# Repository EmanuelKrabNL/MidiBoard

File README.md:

# MIDIBOARD
## What is this project?
Well, basically a simplified mini keyboard for my little sister.
Shes saying she wants to play piano, so i built her one! (Hopefully she wanted to play the piano because her cool brother also plays drums and piano, *rightttt..???*)
-# Im so funny i know right
Okay, back to the plot, i made this becuase she wants a piano (just to press some keys and never touch it again), so we are making here one! (we are so back)

## What does it do?
When you press the 'key looking things', while it is connected to a midi input supporting device, and the midi supporting device is actively running a midi supported application, and the firmware which makes the midi device input for the midi supporting device running the midi supported application is flashed, it should be ready to go! 
-# omg im so funny

## Why is this suited for my little sister?
I have put the letters of the notes on the midi device which is supported by the midi- okay ill stop... ;-; Okay, so, the letters give my little sister an indication of what note she is playing, and i have also decided to make a higher note actually higher! That way she knows how high or low a note will sound like without thinking!

## What can my midiboard do?
The left mechanical switch makes you go an octave lower, the right one makes you go an octave higher, and the middle one plays a random key!
The left slider 'does' the audio/volume, and the right one modulation!
Ive also added lights cause why not!

## Why have i made this?
For my lil sis, *duhhh...*

## What is its purpose?
***insert musical sounds and off key piano notes being played by a grizzly bear***

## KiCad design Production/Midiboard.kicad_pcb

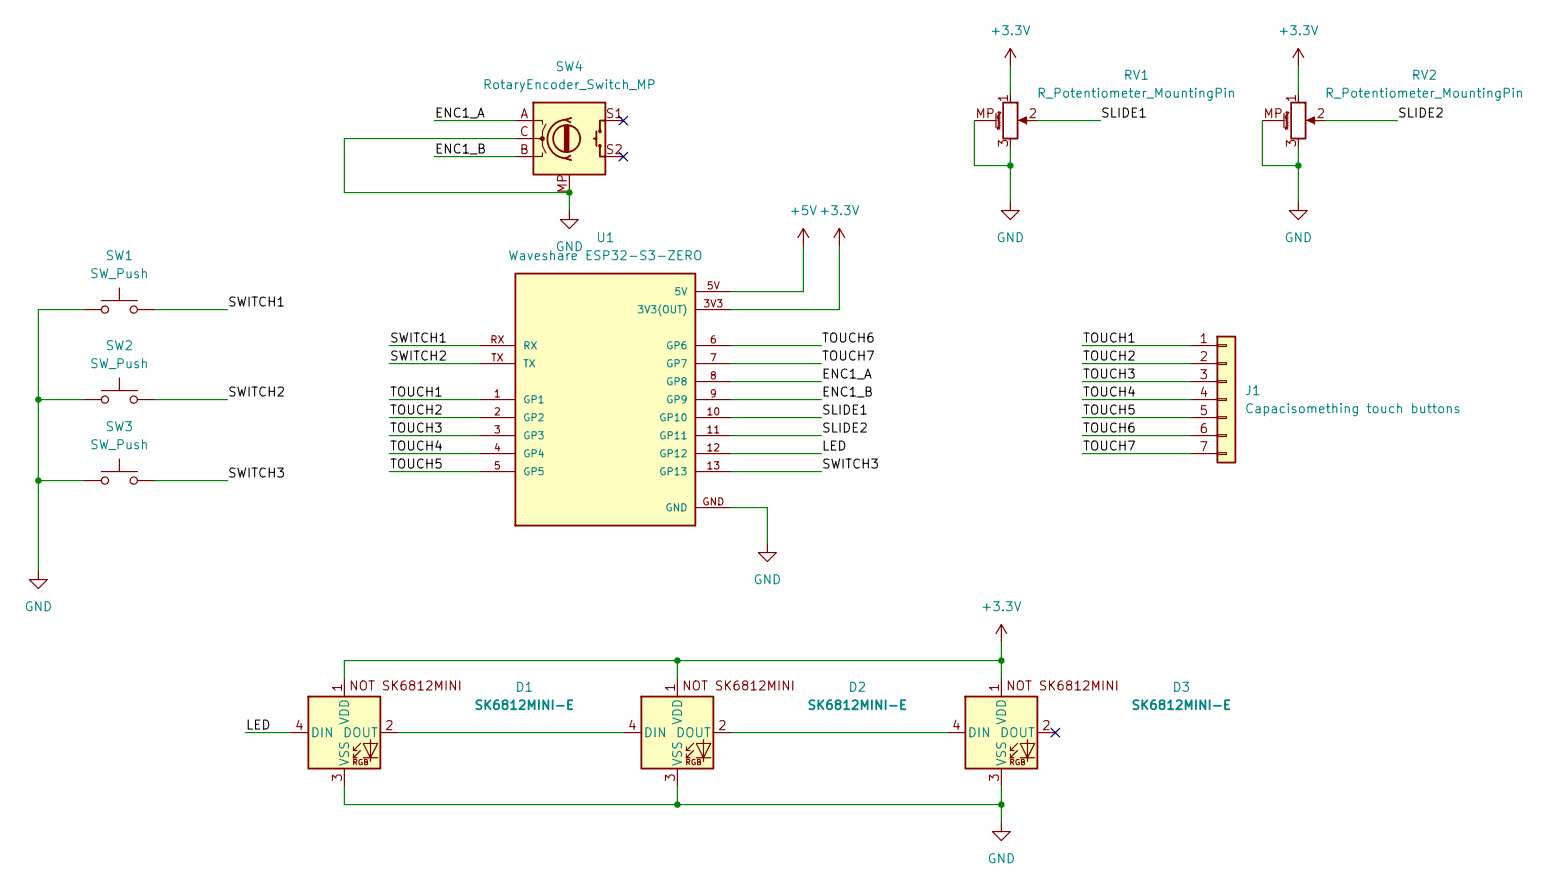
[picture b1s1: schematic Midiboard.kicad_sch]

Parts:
D1, D2, D3: SK6812MINI-E; LED_SK6812MINI-E_3.2x2.8mm_P1.5mm_ReverseMount
J1: Capacisomething touch buttons; Capacitative keys
RV1, RV2: R_Potentiometer_MountingPin; Potentiometer_Bourns_PTA1543_Single_Slide
SW1, SW2, SW3: SW_Push; Kailh Choc Low-Profile Switches
SW4: RotaryEncoder_Switch_MP; RotaryEncoder_Alps_EC11E-Switch_Vertical_H20mm
U1: Waveshare ESP32-S3-ZERO; Waveshare ESP32-S3-Zero; PARTREV NA

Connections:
+3.3V: D1.1 (VDD), D2.1 (VDD), D3.1 (VDD), RV1.1, RV2.1, U1.3V3 (3V3(OUT))
+5V: U1.5V
/ENC1_A: SW4.A, U1.8 (GP8)
/ENC1_B: SW4.B, U1.9 (GP9)
/LED: D1.4 (DIN), U1.12 (GP12)
/SLIDE1: RV1.2, U1.10 (GP10)
/SLIDE2: RV2.2, U1.11 (GP11)
/SWITCH1: SW1.2, U1.RX
/SWITCH2: SW2.2, U1.TX
/SWITCH3: SW3.2, U1.13 (GP13)
/TOUCH1: J1.1, U1.1 (GP1)
/TOUCH2: J1.2, U1.2 (GP2)
/TOUCH3: J1.3, U1.3 (GP3)
/TOUCH4: J1.4, U1.4 (GP4)
/TOUCH5: J1.5, U1.5 (GP5)
/TOUCH6: J1.6, U1.6 (GP6)
/TOUCH7: J1.7, U1.7 (GP7)
GND: D1.3 (VSS), D2.3 (VSS), D3.3 (VSS), RV1.3, RV1.MP (MountPin), RV2.3, RV2.MP (MountPin), SW1.1, SW2.1, SW3.1, SW4.C, SW4.MP, U1.GND
unnamed: D1.2 (DOUT), D2.4 (DIN)
unnamed: D2.2 (DOUT), D3.4 (DIN)

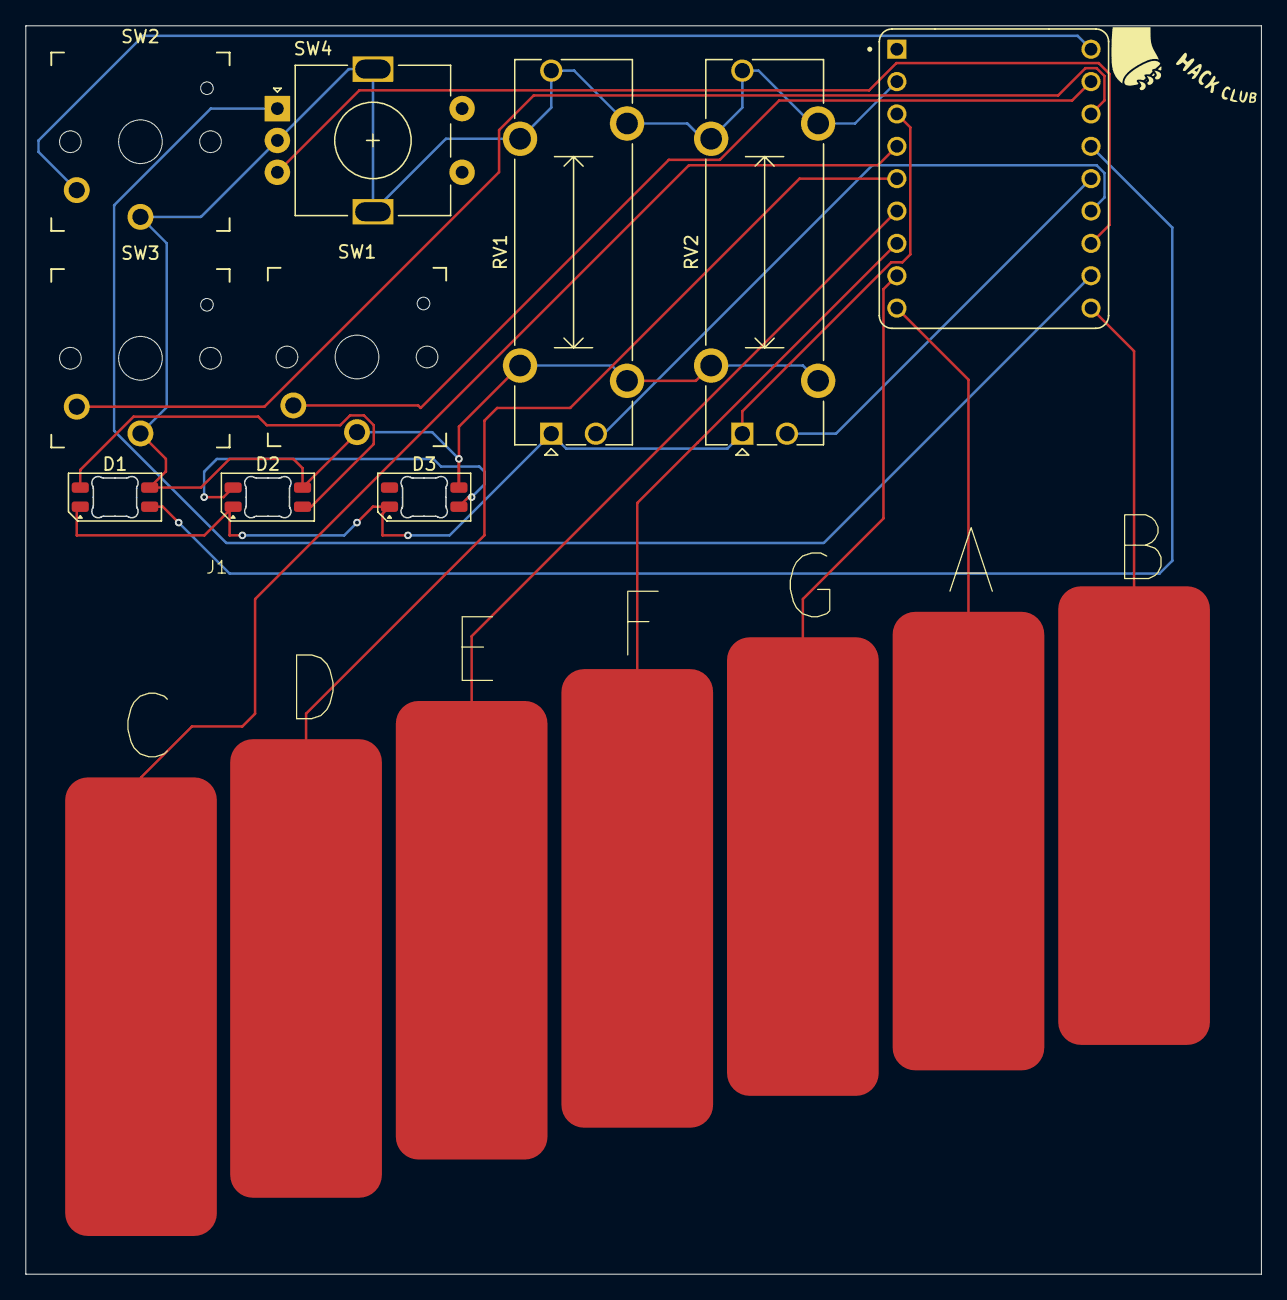
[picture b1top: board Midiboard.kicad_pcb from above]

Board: 2 copper layers, 97.0 x 98.0 mm, 11 parts (0 on the bottom side), 19 nets.

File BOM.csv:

Designator,Footprint,Quantity,Value,Total Cost,Part
"D1, D2, D3",LED_SK6812MINI-E_3.2x2.8mm_P1.5mm_ReverseMount,3 (bought as 20 pack),SK6812MINI-E,€4.99,https://nl.aliexpress.com/item/1005007863635868.html?spm=a2g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
J1,Capacitive Keys,1,Capacitive Touch Buttons,,
"RV1, RV2",Potentiometer_Bourns_PTA1543_Single_Slide,2,Slider,€3.26,https://www.digikey.nl/en/products/detail/bourns-inc/PTA1543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
"SW1, SW2, SW3",Kailh Choc Low-Profile Switches,3,SW_Push,€6.89,https://www.aliexpress.com/item/1005008883418065.html?spm=a2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
SW4,RotaryEncoder_Alps_EC11E-Switch_Vertical_H20mm,1,RotaryEncoder_Switch_MP,$2.59,https://nl.aliexpress.com/item/1005007644083514.html?spm=a2g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
U1,Waveshare ESP32-S3-Zero,1,Waveshare ESP32-S3-ZERO,$7.49,https://nl.aliexpress.com/item/1005007004089798.html?src=goo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
,,,,,
,,,Total Aliexpress:,€21.77,
,,,Total Digikey:,€34.19,
,,,Total JLCPCB: ,$15.89,
,,,Total:,€55.96,
